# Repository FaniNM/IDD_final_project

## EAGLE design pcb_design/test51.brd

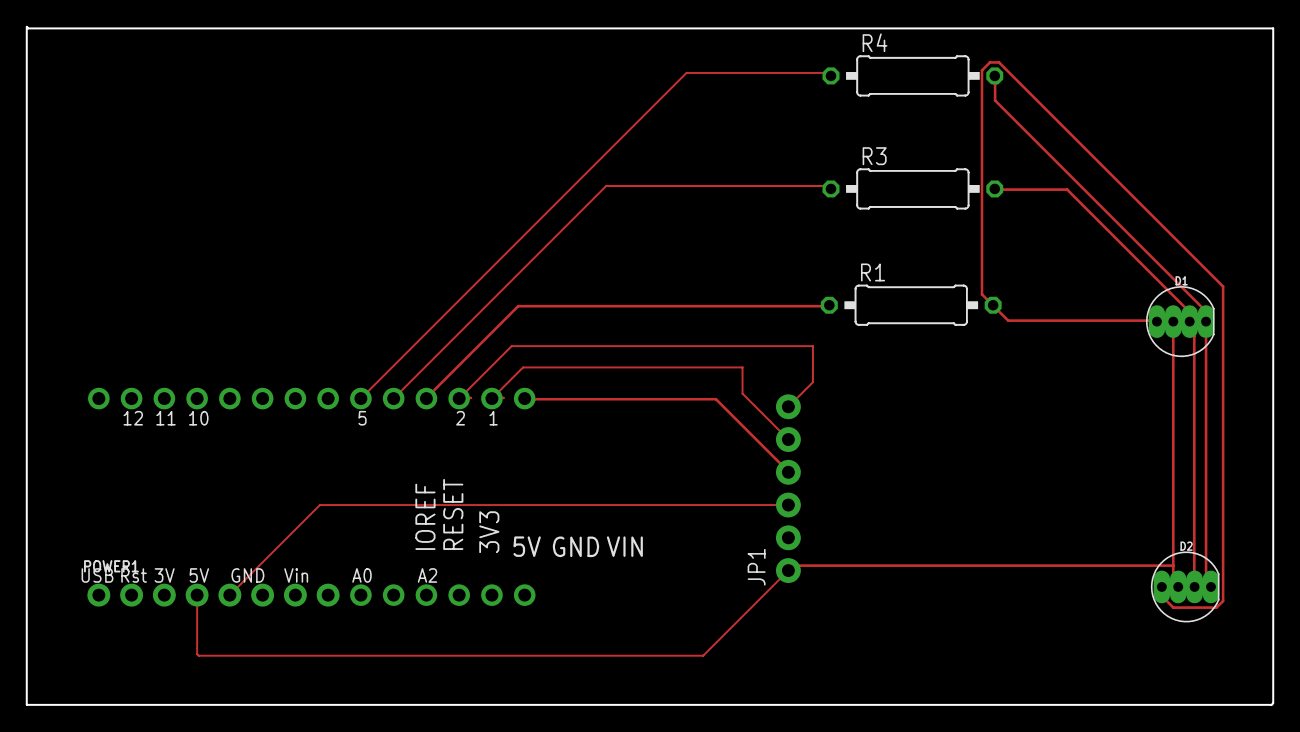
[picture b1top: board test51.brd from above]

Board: 2 copper layers, 96.6 x 52.6 mm, 10 parts (0 on the bottom side), 11 nets.

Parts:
AD, AD1: 20609; 1X06_ROUND
D1, D2: CLEAR; LED-RGB-THRU
IOL: 20610; 1X08_ROUND
JP1: Breakout; 1X06_ROUND_76
POWER1: 20610; 1X08_ROUND_70
R1, R3, R4: 0309/12

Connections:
IO2: IOL.6, JP1.6
unnamed: IOL.5, R1.1
S$1: D1.3, D2.3, JP1.1, POWER1.4
S$3: IOL.7, JP1.5
S$5: JP1.3, POWER1.5
S$6: IOL.8, JP1.4
S$8: IOL.4, R3.1
S$9: IOL.3, R4.1
S$10: D1.1, D2.1, R4.2
S$11: D1.2, D2.2, R3.2
S$12: D1.4, D2.4, R1.2

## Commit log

2018-05-11 first

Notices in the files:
parts and their libraries:
microbuilder: This work is placed in the public domain, and may be freely used for commercial and non-commercial work with the following conditions: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
SparkFun-LED: Licensing: Creative Commons ShareAlike 4.0 International - https://creativecommons.org/licenses/by-sa/4.0
